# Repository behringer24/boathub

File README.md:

# ESP32 BoatHub

Boat monitoring, SeaTalk1 gateway, track logger and NMEA2000 groundwork, built around an
ESP32-S3 N16R8.

A permanently powered ESP32 system monitors the boat in the marina, provides its own on-board
Wi-Fi, pushes measurements over an outbound TLS connection to a self-hosted Docker server, and is
later extended into a gateway for SeaTalk1, autopilot control, track logging and NMEA2000.

Based on the project guide v0.1 of 2026-09-13
([PDF, German](docs/reference/ESP32_BoatHub_Projektanleitung.pdf)).

## What it does, in the order it is built

| | Scope |
|---|-------|
| **v1** | Base monitoring: temperatures, humidity, air pressure, battery, optional bilge level, on-board Wi-Fi, marina Wi-Fi, server uplink |
| **v2** | Read SeaTalk1: log, depth, compass, GPS, autopilot status |
| **v2.5** | Store GPS tracks locally and sync them as a digital logbook |
| **v2B** | Write SeaTalk1: local autopilot control - only after RX runs reliably |
| **v3** | NMEA2000 over TWAI/CAN |
| **v4** | Android tablet or phone running OpenCPN as a plotter |

Software scope in detail: [docs/ROADMAP.md](docs/ROADMAP.md).
Build order: [docs/design/README.md](docs/design/README.md).

## Architecture (target)

```
Sensors (1-Wire / I2C / 4-20 mA)
        |
     ESP32-S3 N16R8  ──SoftAP──>  BOOT-NETZ (Pixel, tablet, OpenCPN)
        |   |
        |   └──STA──> marina Wi-Fi ──TLS──> self-hosted Docker server
        |                                     ├── Mosquitto (MQTT)
   SeaTalk1 (stage 2)                         ├── Backend/API
   NMEA2000 (stage 3)                         ├── PostgreSQL + PostGIS
                                              └── Grafana / web dashboard
```

The ESP opens the internet connection outbound. No inbound ports are needed in the marina network,
and the board does not route between its two networks - `BOOT-NETZ` reaches the board, not the
internet.

**The two networks share one radio.** In AP+STA mode the SoftAP is forced onto whatever channel the
station connects to, so when the marina access point changes channel - many do so automatically -
every device on `BOOT-NETZ` is disconnected. This is normal behaviour, not a fault: clients have to
tolerate reconnects, and no local UI may treat a dropped socket as anything unusual.

## Hardware at a glance

- **Controller:** 1 x ESP32-S3 N16R8 DevKitC-1 (third-party module). It sits on the bundled
  screw-terminal carrier for the bench build and in a socket on the main board once installed -
  [A-001](docs/design/A-001-devkit-and-carrier.md),
  [B-002](docs/design/B-002-main-board.md). Ships with an onboard PCB antenna; the bundled external
  antenna needs a solder rework to activate
- **Temperature:** 3 x DS18B20 (engine bay, bilge water, fridge), each on its own 1-Wire GPIO
- **Cabin climate:** SHT31-D (I2C, address 0x44)
- **Barometer and battery bay:** BME680 (I2C, address 0x76) on a short cable in the battery bay -
  air pressure for the weather trend, and the bay's air temperature and humidity. Its gas heater
  stays off - [A-010](docs/design/A-010-bme680-barometer-and-battery-bay.md)
- **Analog:** 2 x ADS1115 on the shared I2C bus, 0x48 and 0x49. The second is socketed and may
  stay empty until its channels are specified
- **Attitude and motion:** LSM6DSOX IMU on the I2C bus at 0x6A, with its interrupt on GPIO2 -
  heel and pitch under sail, impacts at the berth
- **Battery:** 100 kΩ / 10 kΩ divider (factor 11.0) into ADS1115 A0, tapped **upstream of** the
  reverse-polarity diode, calibrated against a multimeter
- **Bilge level (optional):** hydrostatic 0-1 m probe, 4-20 mA, 100 Ω burden into ADS1115 A1
- **Power:** 12 V house supply → 2 A fuse → TVS 1.5KE20A → 1N5822 → DC/DC 9-36 V to 5 V

The TVS sits ahead of the Schottky diode, and the battery tap ahead of both - see
[docs/design/B-001-power-supply.md](docs/design/B-001-power-supply.md) for why the order matters.

Full parts list with prices and sources: [docs/MATERIAL.md](docs/MATERIAL.md)

### Pin assignment

| GPIO | Function today | Later / note |
|------|----------------|--------------|
| 2 | IMU interrupt | impact detection, [A-009](docs/design/A-009-imu-heel-and-motion.md) |
| 4 | DS18B20 engine bay | dedicated 1-Wire bus |
| 5 | DS18B20 bilge water | dedicated 1-Wire bus |
| 6 | DS18B20 fridge | dedicated 1-Wire bus |
| 7 | spare | optional water tank DS18B20 |
| 8 | I2C SDA | SHT31, BME680, both ADS1115, IMU |
| 9 | I2C SCL | SHT31, BME680, both ADS1115, IMU |
| 15 | reserved | SeaTalk RX (stage 2) |
| 16 | reserved | SeaTalk TX (stage 2) |
| 17 | reserved | TWAI TX (stage 3) |
| 18 | reserved | TWAI RX (stage 3) |
| 21 | spare | optional local buzzer - **through a transistor**, 20-30 mA exceeds the GPIO limit |
| 43/44 | debug UART | keep free for servicing |
| 48 | onboard WS2812 RGB LED | DevKit-internal, confirmed on the delivered board - do not reuse |

Avoided: strapping pins GPIO0/3/45/46, USB pins GPIO19/20, and GPIO33-37 on the N16R8 (octal
PSRAM). Always cross-check the silkscreen of the delivered DevKit board before soldering.

## Safety rules

- **12 V is not harmless.** A boat battery can deliver very high short-circuit currents. Every new
  feed gets its own fuse close to the source.
- **Never feed 5 V into 3V3.** USB and the 5V pin may supply the DevKit at the same time: each
  feeds it through a diode of its own, so the higher one carries the load and neither drives the
  other. On the main board USB and the 12 V side can therefore be connected together, and the
  DevKit stays in its socket to be flashed or debugged - **as long as the DevKit's IN-OUT and
  USB-OTG solder pads stay open**.
- **SeaTalk TX stays disabled** until RX runs reliably and the output stage has been tested
  separately on the bench. After a reset or a lost connection the transmit path is passive.
- **No autopilot commands from the internet.** Control lives on the local on-board Wi-Fi only; the
  server receives telemetry.
- No Wi-Fi or server passwords in source code. Configuration lives in NVS/Preferences.
- **Sensor and network faults are decoupled.** A broken probe, a silent broker or a marina access
  point that vanishes may cost its own reading or its own connection, and nothing else. The
  watchdog is there for what gets past that.
- The boat is permanently on shore power in the marina, so the BoatHub runs continuously. On the
  2 x 100 Ah AGM bank (~100 Ah usable, no solar or wind) it would still draw 40-60 Ah per month on
  its own, so a **low-voltage backstop stays mandatory** for the case shore power fails and stays
  failed - the remaining capacity belongs to the bilge pump.
- The shore-power-loss alarm is gated on at least 6 hours of prior charging, so it stays quiet
  underway where running on the battery is normal. See
  [docs/design/B-001-power-supply.md](docs/design/B-001-power-supply.md).
- **Alarms are judged on the board and acknowledged only at the box**, with the BOOT button. The
  server stores and shows the events; nothing it sends can silence or clear an alarm. See
  [docs/design/A-012-alarm-and-threshold-logic.md](docs/design/A-012-alarm-and-threshold-logic.md).

## Repository layout

```
board/                  PlatformIO firmware project - ESP32-S3 N16R8, see board/platformio.ini
hardware/
├── main-board/         KiCad project, see docs/design/B-002-main-board.md
│   └── fab/<rev>/      what was actually sent to the fabricator, one directory per revision
└── case/               parametric FreeCAD model of a printed enclosure, run rather than
                        drawn, see hardware/case/README.md
server/                 MQTT broker in Docker, see server/README.md
docs/
├── ROADMAP.md          planned software functionality, board and server
├── CHANGELOG.md        software change log
├── MATERIAL.md         bill of materials and tools
├── operating-card.html two printable pages for on board: LED, buttons, settings, cable colours
├── design/             build guide and one document per feature (+ TEMPLATE.md)
│   ├── A-NNN-*.md      phase A: the bench build on USB power
│   ├── B-NNN-*.md      phase B: 12 V supply, protection, the main board
│   └── D-NNN-*.md      phase D: SeaTalk1
├── reference/          source documents (project guide PDF)
```

## Where to start

Read [docs/design/A-001-devkit-and-carrier.md](docs/design/A-001-devkit-and-carrier.md) to identify
the board and its carrier, then build along
[docs/design/A-002-bench-setup-usb.md](docs/design/A-002-bench-setup-usb.md).

**Phase A runs entirely on USB power - no 12 V anywhere.** The 12 V supply is built only once the
whole sensor and network stack has run 24 hours on USB without intervention, so that a brownout
later can be blamed on the converter rather than on the firmware. The full build order is in
[docs/design/README.md](docs/design/README.md).

Once it is installed, print [docs/operating-card.html](docs/operating-card.html) from a browser and
keep it with the box: what the LED and the two buttons mean, what every setting on the
configuration page does, and the cable colours.

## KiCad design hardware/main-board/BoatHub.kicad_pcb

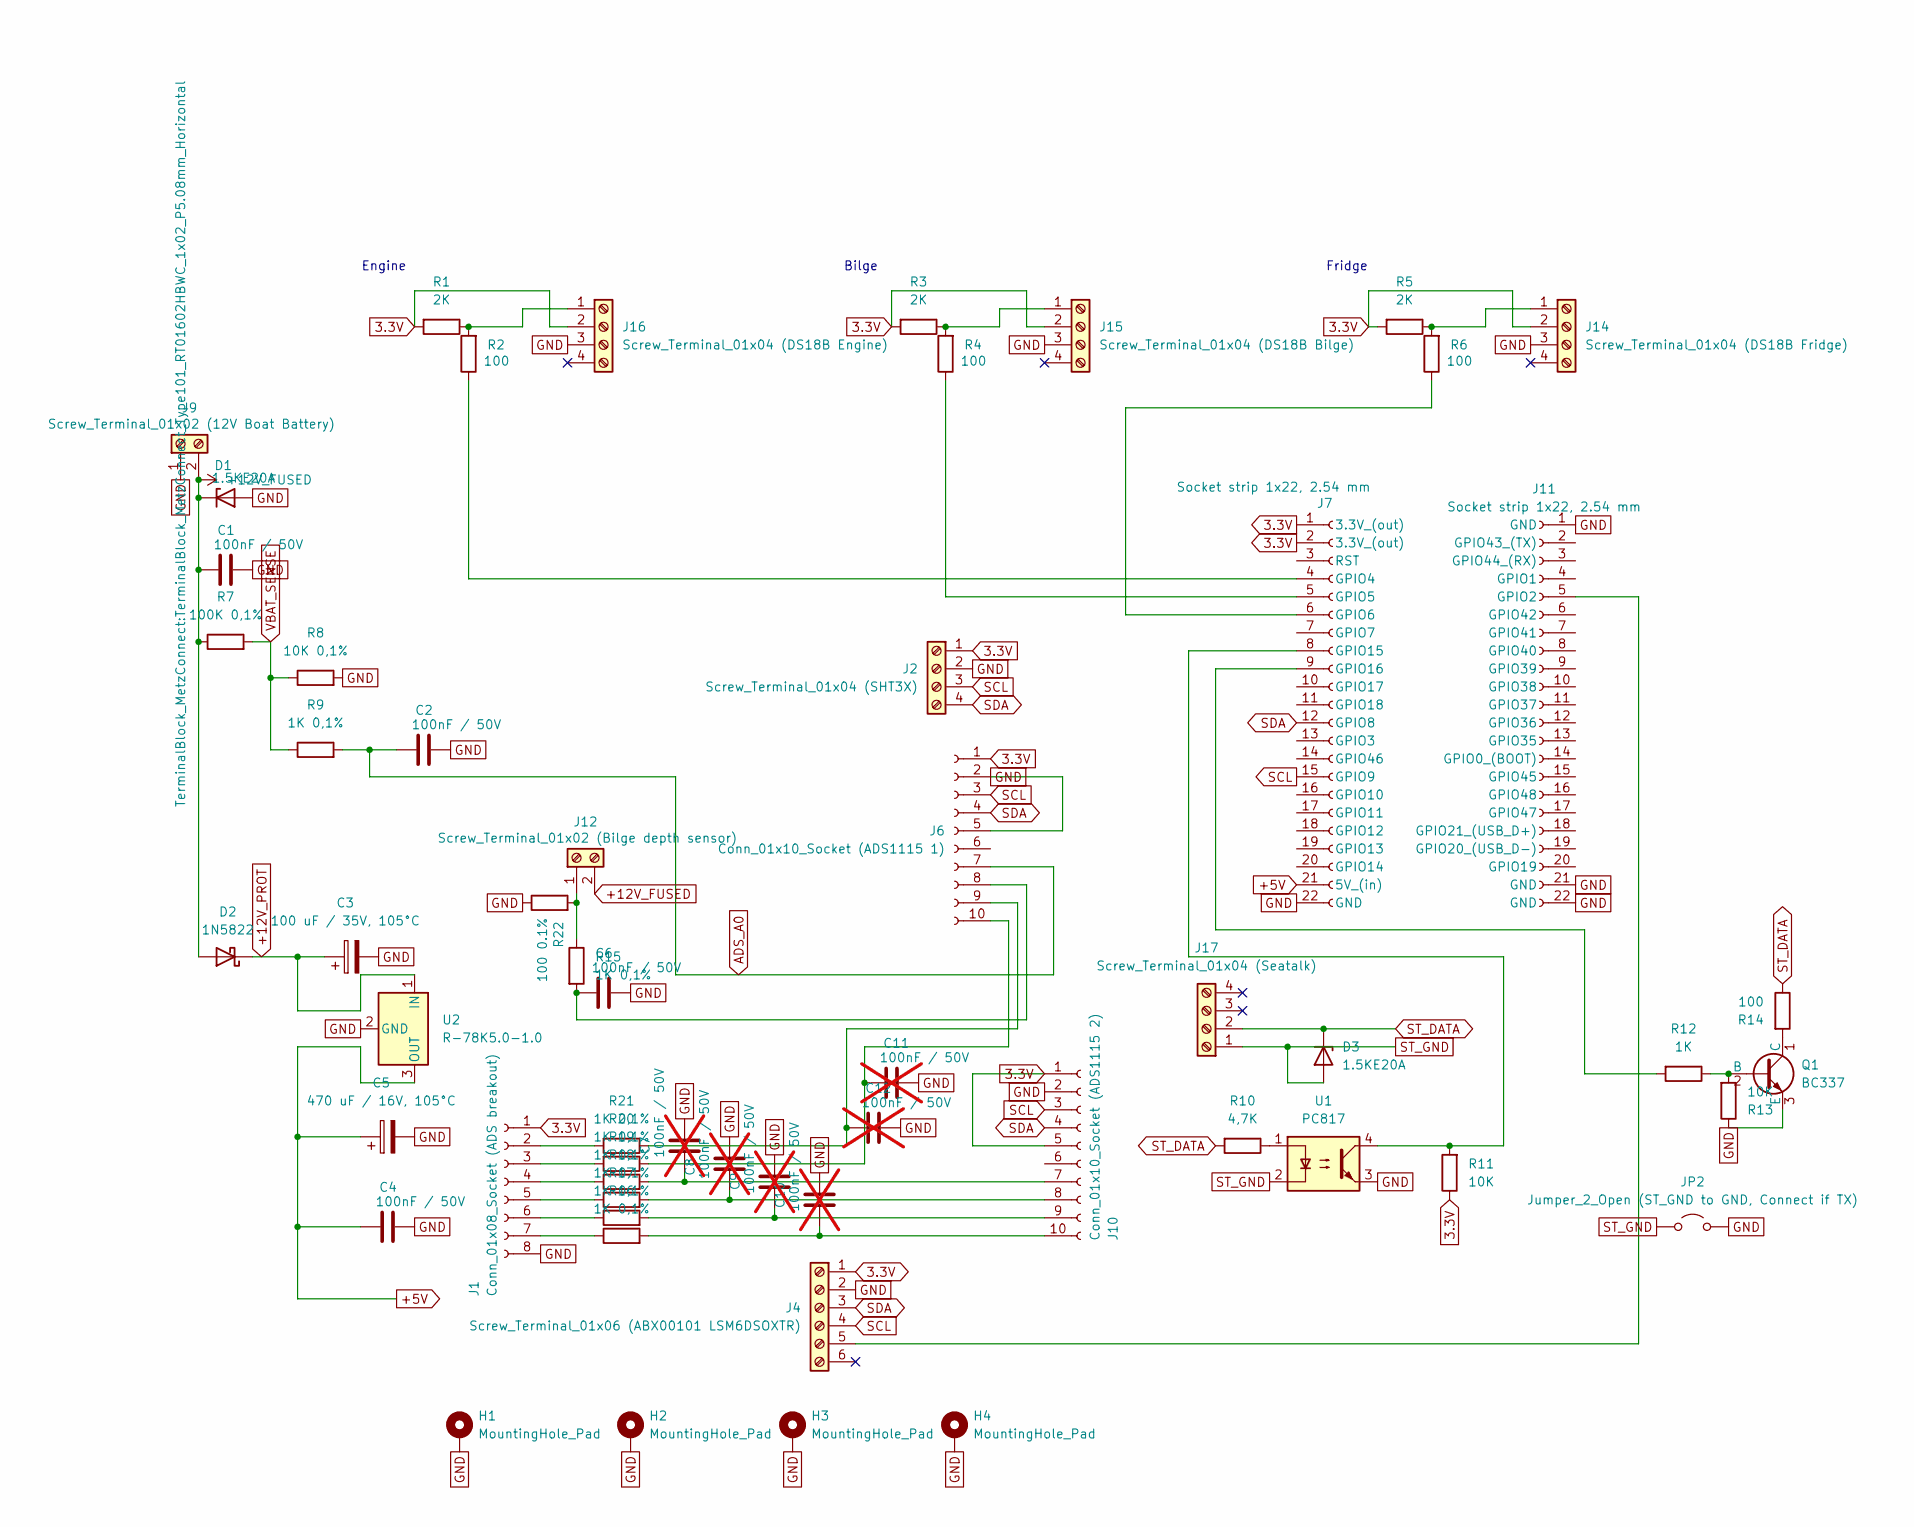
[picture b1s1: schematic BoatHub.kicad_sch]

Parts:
C1, C2, C4, C6: 100nF / 50V; C_Disc_D5.0mm_W2.5mm_P5.00mm
C3: 100 uF / 35V, 105°C; CP_Radial_D8.0mm_P3.50mm
C5: 470 uF / 16V, 105°C; CP_Radial_D10.0mm_P5.00mm
C7, C8, C9, C10, C11, C12: 100nF / 50V; C_Disc_D5.0mm_W2.5mm_P5.00mm; not fitted
D1, D3: 1.5KE20A; D_DO-201AE_P15.24mm_Horizontal
D2: 1N5822; D_DO-201AD_P15.24mm_Horizontal
H1, H2, H3, H4: MountingHole_Pad; MountingHole_3.2mm_M3_Pad
J1: Conn_01x08_Socket (ADS breakout); PinSocket_1x08_P2.54mm_Vertical
J2: Screw_Terminal_01x04 (SHT3X); TerminalBlock_MetzConnect_Type101_RT01604HBWC_1x04_P5.08mm_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
J4: Screw_Terminal_01x06 (ABX00101 LSM6DSOXTR); TerminalBlock_MetzConnect_Type101_RT01606HBWC_1x06_P5.08mm_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
J6: Conn_01x10_Socket (ADS1115 1); PinSocket_1x10_P2.54mm_Vertical
J7, J11: Socket strip 1x22, 2.54 mm; PinSocket_1x22_P2.54mm_Vertical
J9: Screw_Terminal_01x02 (12V Boat Battery); TerminalBlock_MetzConnect_Type101_RT01602HBWC_1x02_P5.08mm_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
J10: Conn_01x10_Socket (ADS1115 2); PinSocket_1x10_P2.54mm_Vertical
J12: Screw_Terminal_01x02 (Bilge depth sensor); TerminalBlock_MetzConnect_Type101_RT01602HBWC_1x02_P5.08mm_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
J14: Screw_Terminal_01x04 (DS18B Fridge); TerminalBlock_MetzConnect_Type101_RT01604HBWC_1x04_P5.08mm_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
J15: Screw_Terminal_01x04 (DS18B Bilge); TerminalBlock_MetzConnect_Type101_RT01604HBWC_1x04_P5.08mm_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
J16: Screw_Terminal_01x04 (DS18B Engine); TerminalBlock_MetzConnect_Type101_RT01604HBWC_1x04_P5.08mm_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
J17: Screw_Terminal_01x04 (Seatalk); TerminalBlock_MetzConnect_Type101_RT01604HBWC_1x04_P5.08mm_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
JP2: Jumper_2_Open (ST_GND to GND, Connect if TX); TestPoint_2Pads_Pitch2.54mm_Drill0.8mm
Q1: BC337; TO-92_Inline
R1, R3, R5: 2K; R_Axial_DIN0309_L9.0mm_D3.2mm_P12.70mm_Horizontal
R2, R4, R6: 100; R_Axial_DIN0309_L9.0mm_D3.2mm_P12.70mm_Horizontal
R7: 100K 0,1%; R_Axial_DIN0207_L6.3mm_D2.5mm_P10.16mm_Horizontal
R8: 10K 0,1%; R_Axial_DIN0207_L6.3mm_D2.5mm_P10.16mm_Horizontal
R9, R15, R16, R17, R18, R19, R20, R21: 1K 0,1%; R_Axial_DIN0207_L6.3mm_D2.5mm_P10.16mm_Horizontal
R10: 4,7K; R_Axial_DIN0207_L6.3mm_D2.5mm_P10.16mm_Horizontal
R11, R13: 10K; R_Axial_DIN0207_L6.3mm_D2.5mm_P10.16mm_Horizontal
R12: 1K; R_Axial_DIN0207_L6.3mm_D2.5mm_P10.16mm_Horizontal
R14: 100; R_Axial_DIN0207_L6.3mm_D2.5mm_P10.16mm_Horizontal
R22: 100 0.1%; R_Axial_DIN0309_L9.0mm_D3.2mm_P12.70mm_Horizontal
U1: PC817; DIP-4_W7.62mm
U2: R-78K5.0-1.0; Converter_DCDC_RECOM_R-78E-0.5_THT

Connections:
3.3V: J1.1, J2.1, J4.1, J6.1, J7.1 (3.3V_(out)), J7.2 (3.3V_(out)), J10.1, J10.5, J14.2, J15.2, J16.2, R1.2, R3.2, R5.2, R11.1
+5V: C4.2, C5.1, J7.21 (5V_(in)), U2.3 (OUT)
+12V_FUSED: C1.2, D1.1 (K), D2.2 (A), J9.2, J12.2, R7.1
+12V_PROT: C3.1, D2.1 (K), U2.1 (IN)
ADS_A0: C2.2, J6.7, R9.2
GND: C1.1, C2.1, C3.2, C4.1, C5.2, C6.1, C7.1, C8.1, C9.1, C10.1, C11.1, C12.1, D1.2 (A), H1.1 (1_1), H2.1 (1_1), H3.1 (1_1), H4.1 (1_1), J1.8, J2.2, J4.2, J6.2, J6.5, J7.22 (GND), J9.1, J10.2, J11.1 (GND), J11.21 (GND), J11.22 (GND), J14.3, J15.3, J16.3, JP2.2 (B), Q1.3 (E), R8.2, R13.1, R22.1, U1.3, U2.2 (GND)
unnamed: J1.2, R21.2
unnamed: J1.3, R20.2
unnamed: J1.4, R19.1
unnamed: J1.5, R18.1
unnamed: J1.6, R17.1
unnamed: J1.7, R16.1
unnamed: C6.2, J6.8, R15.2
unnamed: C12.2, J6.9, R21.1
unnamed: C11.2, J6.10, R20.1
unnamed: J7.4 (GPIO4), R2.1
unnamed: J7.5 (GPIO5), R4.1
unnamed: J7.6 (GPIO6), R6.1
unnamed: J7.8 (GPIO15), R11.2, U1.4
unnamed: J7.9 (GPIO16), R12.2
unnamed: C7.2, J10.7, R19.2
unnamed: C8.2, J10.8, R18.2
unnamed: C9.2, J10.9, R17.2
unnamed: C10.2, J10.10, R16.2
unnamed: J4.5, J11.5 (GPIO2)
unnamed: J12.1, R15.1, R22.2
unnamed: J14.1, R5.1, R6.2
unnamed: J15.1, R3.1, R4.2
unnamed: J16.1, R1.1, R2.2
unnamed: Q1.2 (B), R12.1, R13.2
unnamed: Q1.1 (C), R14.2
unnamed: R10.1, U1.1
SCL: J2.3, J4.4, J6.3, J7.15 (GPIO9), J10.3
SDA: J2.4, J4.3, J6.4, J7.12 (GPIO8), J10.4
ST_DATA: D3.1 (K), J17.2, R10.2, R14.1
ST_GND: D3.2 (A), J17.1, JP2.1 (A), U1.2
VBAT_SENSE: R7.2, R8.1, R9.1

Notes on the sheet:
Bilge
Fridge
Engine

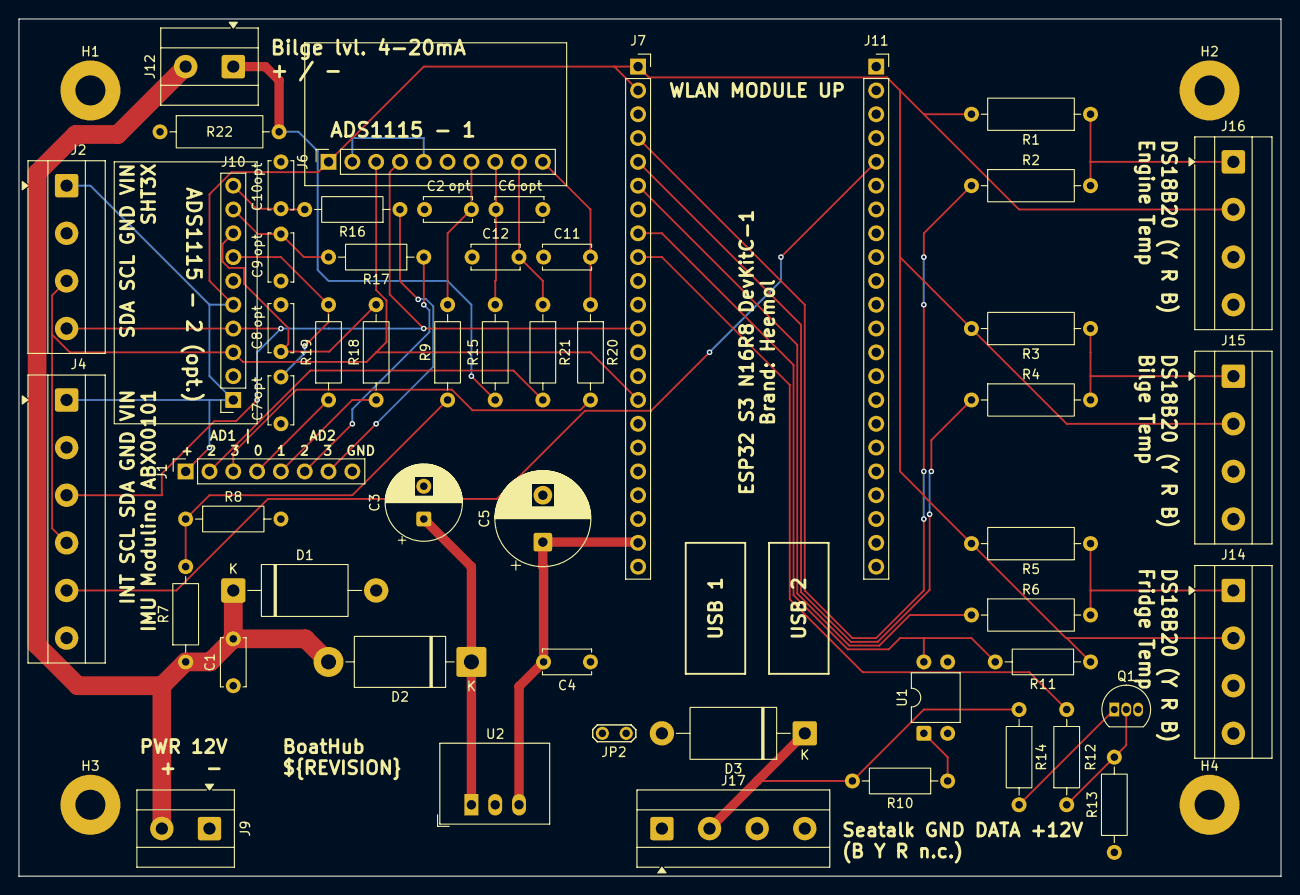
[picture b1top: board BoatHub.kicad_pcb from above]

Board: 2 copper layers, 134.6 x 91.4 mm, 58 parts (0 on the bottom side), 37 nets.
